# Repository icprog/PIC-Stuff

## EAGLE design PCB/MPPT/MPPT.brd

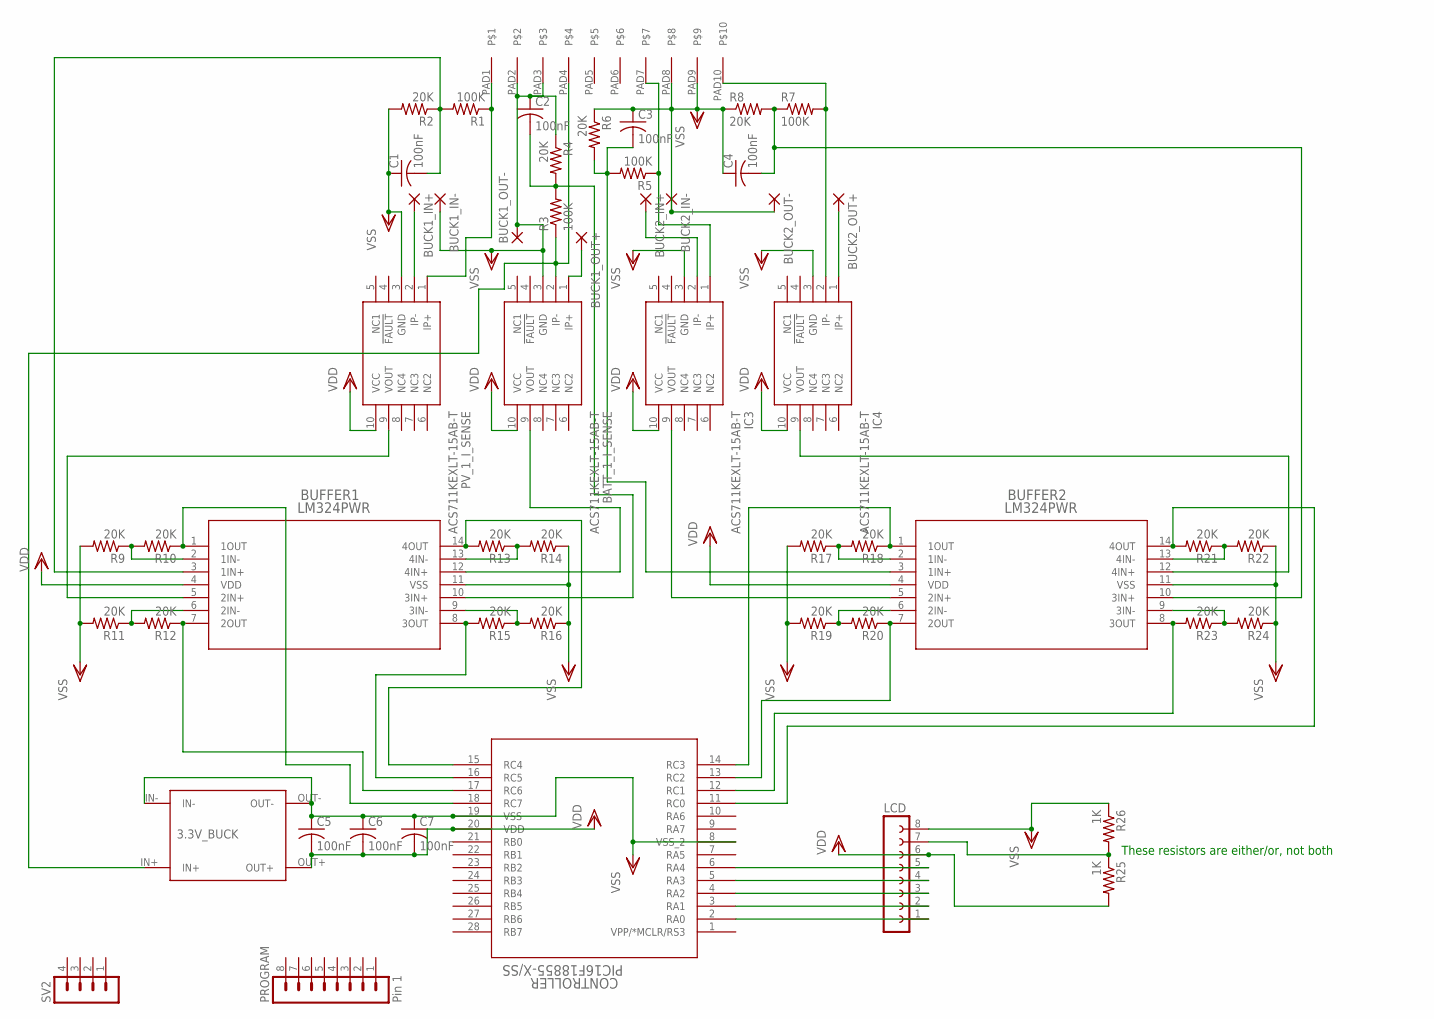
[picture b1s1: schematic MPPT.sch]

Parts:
3.3V_BUCK: TINY_BUCK
BATT_1_I_SENSE: ACS711KEXLT-15AB-T; EX-PACKAGE
BUCK1_IN+, BUCK1_IN-, BUCK1_OUT+, BUCK1_OUT-, BUCK2_IN+, BUCK2_IN-, BUCK2_OUT+, BUCK2_OUT-: 3,81/1,4
BUFFER1, BUFFER2: LM324PWR; PW14
C1, C2, C3, C4, C5, C6, C7: 100nF; C0603
CONTROLLER: PIC16F18855-X/SS; SSOP28_MC
IC3, IC4: ACS711KEXLT-15AB-T; EX-PACKAGE
LCD: FE08
PROGRAM: Pin 1; MA08-1
PV_1_I_SENSE: ACS711KEXLT-15AB-T; EX-PACKAGE
R1, R3, R5, R7: 100K; R0603
R2, R4, R6, R8, R9, R10, R11, R12, R13, R14, R15, R16, R17, R18, R19, R20, R21, R22, R23, R24: 20K; R0603
R25, R26: 1K; R0603
SV2: MA04-1
U$1: CONN-KF2EDG-10(5.08)E-BAYPLUGGABLECONNECTORS; CONN-KF2EDG-10(5.08)

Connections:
unnamed: PV_1_I_SENSE.1 (IP+), R1.1, U$1.PAD1
unnamed: BUFFER1.5 (2IN+), PV_1_I_SENSE.9 (VOUT)
unnamed: BUFFER1.3 (1IN+), C1.2, R1.2, R2.1
unnamed: BATT_1_I_SENSE.1 (IP+), BUCK1_OUT+.1
unnamed: BUFFER1.10 (3IN+), C2.2, R3.2, R4.2
unnamed: 3.3V_BUCK.IN+, BATT_1_I_SENSE.2 (IP-), R3.1, U$1.PAD4
unnamed: BUCK2_OUT+.1, IC4.1 (IP+)
unnamed: IC3.1 (IP+), R5.1, U$1.PAD7
unnamed: BUCK2_IN+.1, IC3.2 (IP-)
unnamed: BUFFER2.3 (1IN+), C3.2, R5.2, R6.2
unnamed: IC4.2 (IP-), R7.2, U$1.PAD10
unnamed: BUFFER2.10 (3IN+), C4.2, R7.1, R8.2
unnamed: BUCK1_IN+.1, PV_1_I_SENSE.2 (IP-)
unnamed: BUFFER1.9 (3IN-), R15.1, R16.2
unnamed: BUFFER1.1 (1OUT), CONTROLLER.18 (RC7), R10.1
unnamed: BUFFER1.6 (2IN-), R11.1, R12.2
unnamed: BUFFER1.7 (2OUT), CONTROLLER.17 (RC6), R12.1
unnamed: BUFFER1.13 (4IN-), R13.1, R14.2
unnamed: BUFFER1.2 (1IN-), R9.1, R10.2
unnamed: BUFFER1.14 (4OUT), CONTROLLER.15 (RC4), R13.2
unnamed: BUFFER1.8 (3OUT), CONTROLLER.16 (RC5), R15.2
unnamed: BATT_1_I_SENSE.9 (VOUT), BUFFER1.12 (4IN+)
unnamed: CONTROLLER.2 (RA0), LCD.1
unnamed: BUFFER2.1 (1OUT), CONTROLLER.14 (RC3), R18.1
unnamed: BUFFER2.7 (2OUT), CONTROLLER.13 (RC2), R20.1
unnamed: BUFFER2.6 (2IN-), R19.1, R20.2
unnamed: BUFFER2.14 (4OUT), CONTROLLER.11 (RC0), R21.2
unnamed: BUFFER2.13 (4IN-), R21.1, R22.2
unnamed: BUFFER2.8 (3OUT), CONTROLLER.12 (RC1), R23.2
unnamed: BUFFER2.9 (3IN-), R23.1, R24.2
unnamed: BUFFER2.2 (1IN-), R17.1, R18.2
unnamed: BUFFER2.5 (2IN+), IC3.9 (VOUT)
unnamed: BUFFER2.12 (4IN+), IC4.9 (VOUT)
unnamed: CONTROLLER.3 (RA1), LCD.2
unnamed: CONTROLLER.4 (RA2), LCD.3
unnamed: CONTROLLER.5 (RA3), LCD.4
unnamed: CONTROLLER.6 (RA4), LCD.5
unnamed: LCD.7, R25.1, R26.2
unnamed 38: CONTROLLER.22 (RB1); also elsewhere on the board
unnamed 39: CONTROLLER.21 (RB0); also elsewhere on the board
VDD: 3.3V_BUCK.OUT+, BATT_1_I_SENSE.10 (VCC), BUFFER1.4 (VDD), BUFFER2.4 (VDD), C5.2, C6.2, C7.2, CONTROLLER.20 (VDD), IC3.10 (VCC), IC4.10 (VCC), LCD.6, PV_1_I_SENSE.10 (VCC), R25.2; also elsewhere on the board
VSS: 3.3V_BUCK.IN-, 3.3V_BUCK.OUT-, BATT_1_I_SENSE.3 (GND), BUCK1_IN-.1, BUCK1_OUT-.1, BUCK2_IN-.1, BUCK2_OUT-.1, BUFFER1.11 (VSS), BUFFER2.11 (VSS), C1.1, C2.1, C3.1, C4.1, C5.1, C6.1, C7.1, CONTROLLER.8 (VSS_2), CONTROLLER.19 (VSS), IC3.3 (GND), IC4.3 (GND), LCD.8, PV_1_I_SENSE.3 (GND), R2.2, R4.1, R6.1, R8.1, R9.2, R11.2, R14.1, R16.1, R17.2, R19.2, R22.1, R24.1, R26.1, U$1.PAD2, U$1.PAD3, U$1.PAD8, U$1.PAD9; also elsewhere on the board

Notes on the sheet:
These resistors are either/or, not both

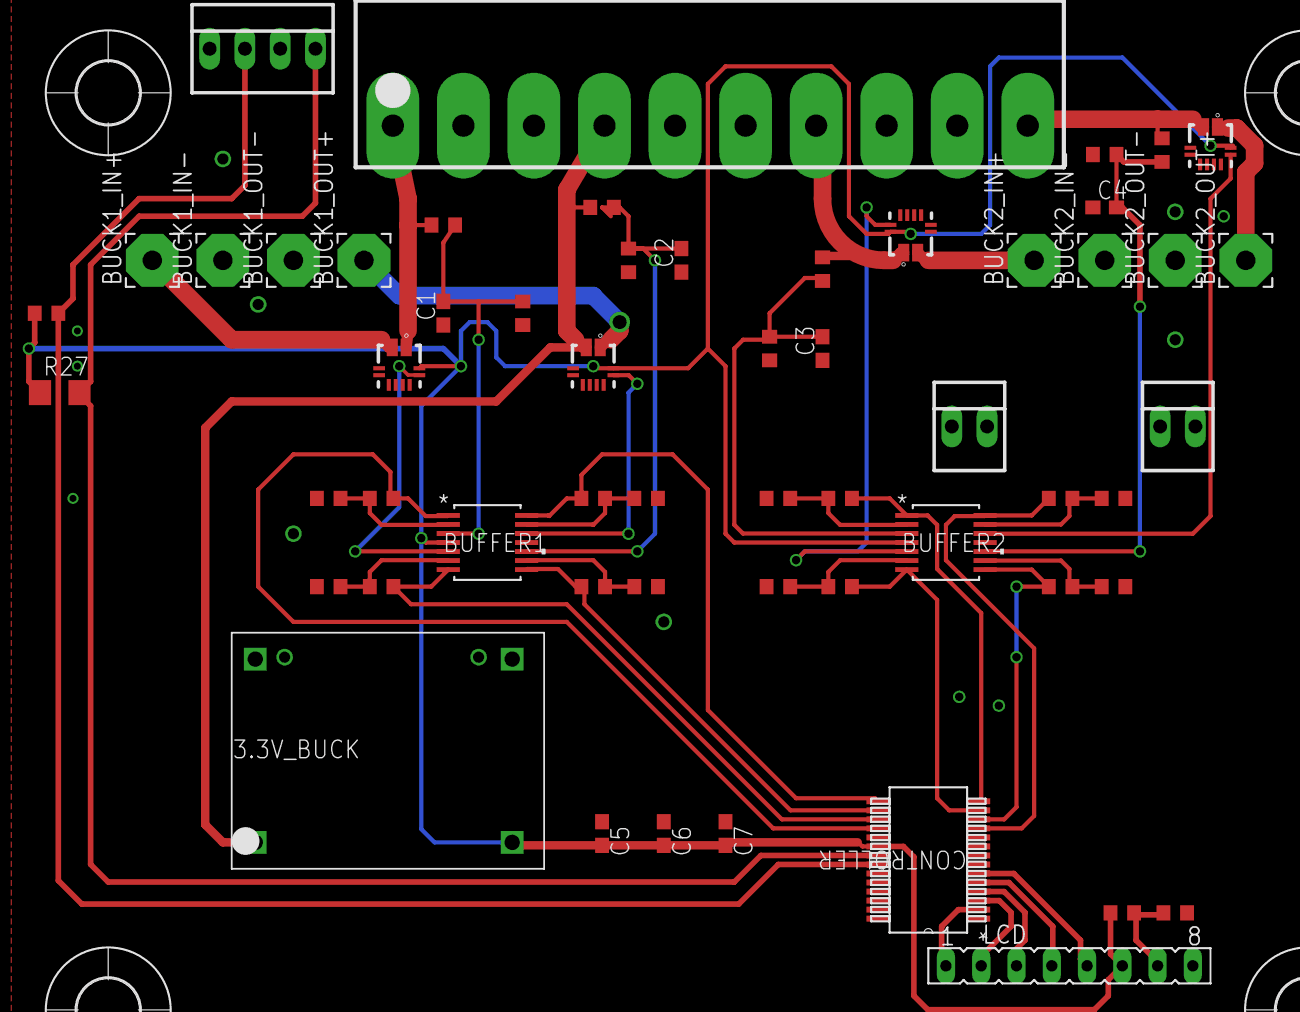
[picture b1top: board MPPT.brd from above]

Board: 2 copper layers, 60 parts (0 on the bottom side), 42 nets.

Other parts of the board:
R27: 10K; R1206
R28: 10K; R0603
U$2, U$3, U$4, U$5: 4,5
X1, X2: 22-23-2021
X3: 22-23-2041

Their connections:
unnamed 38: R28.2, X3.2; also elsewhere on the board
unnamed 39: R27.2, X3.4; also elsewhere on the board
VDD: R27.1, R28.1; also elsewhere on the board
VSS: X3.1, X3.3; also elsewhere on the board

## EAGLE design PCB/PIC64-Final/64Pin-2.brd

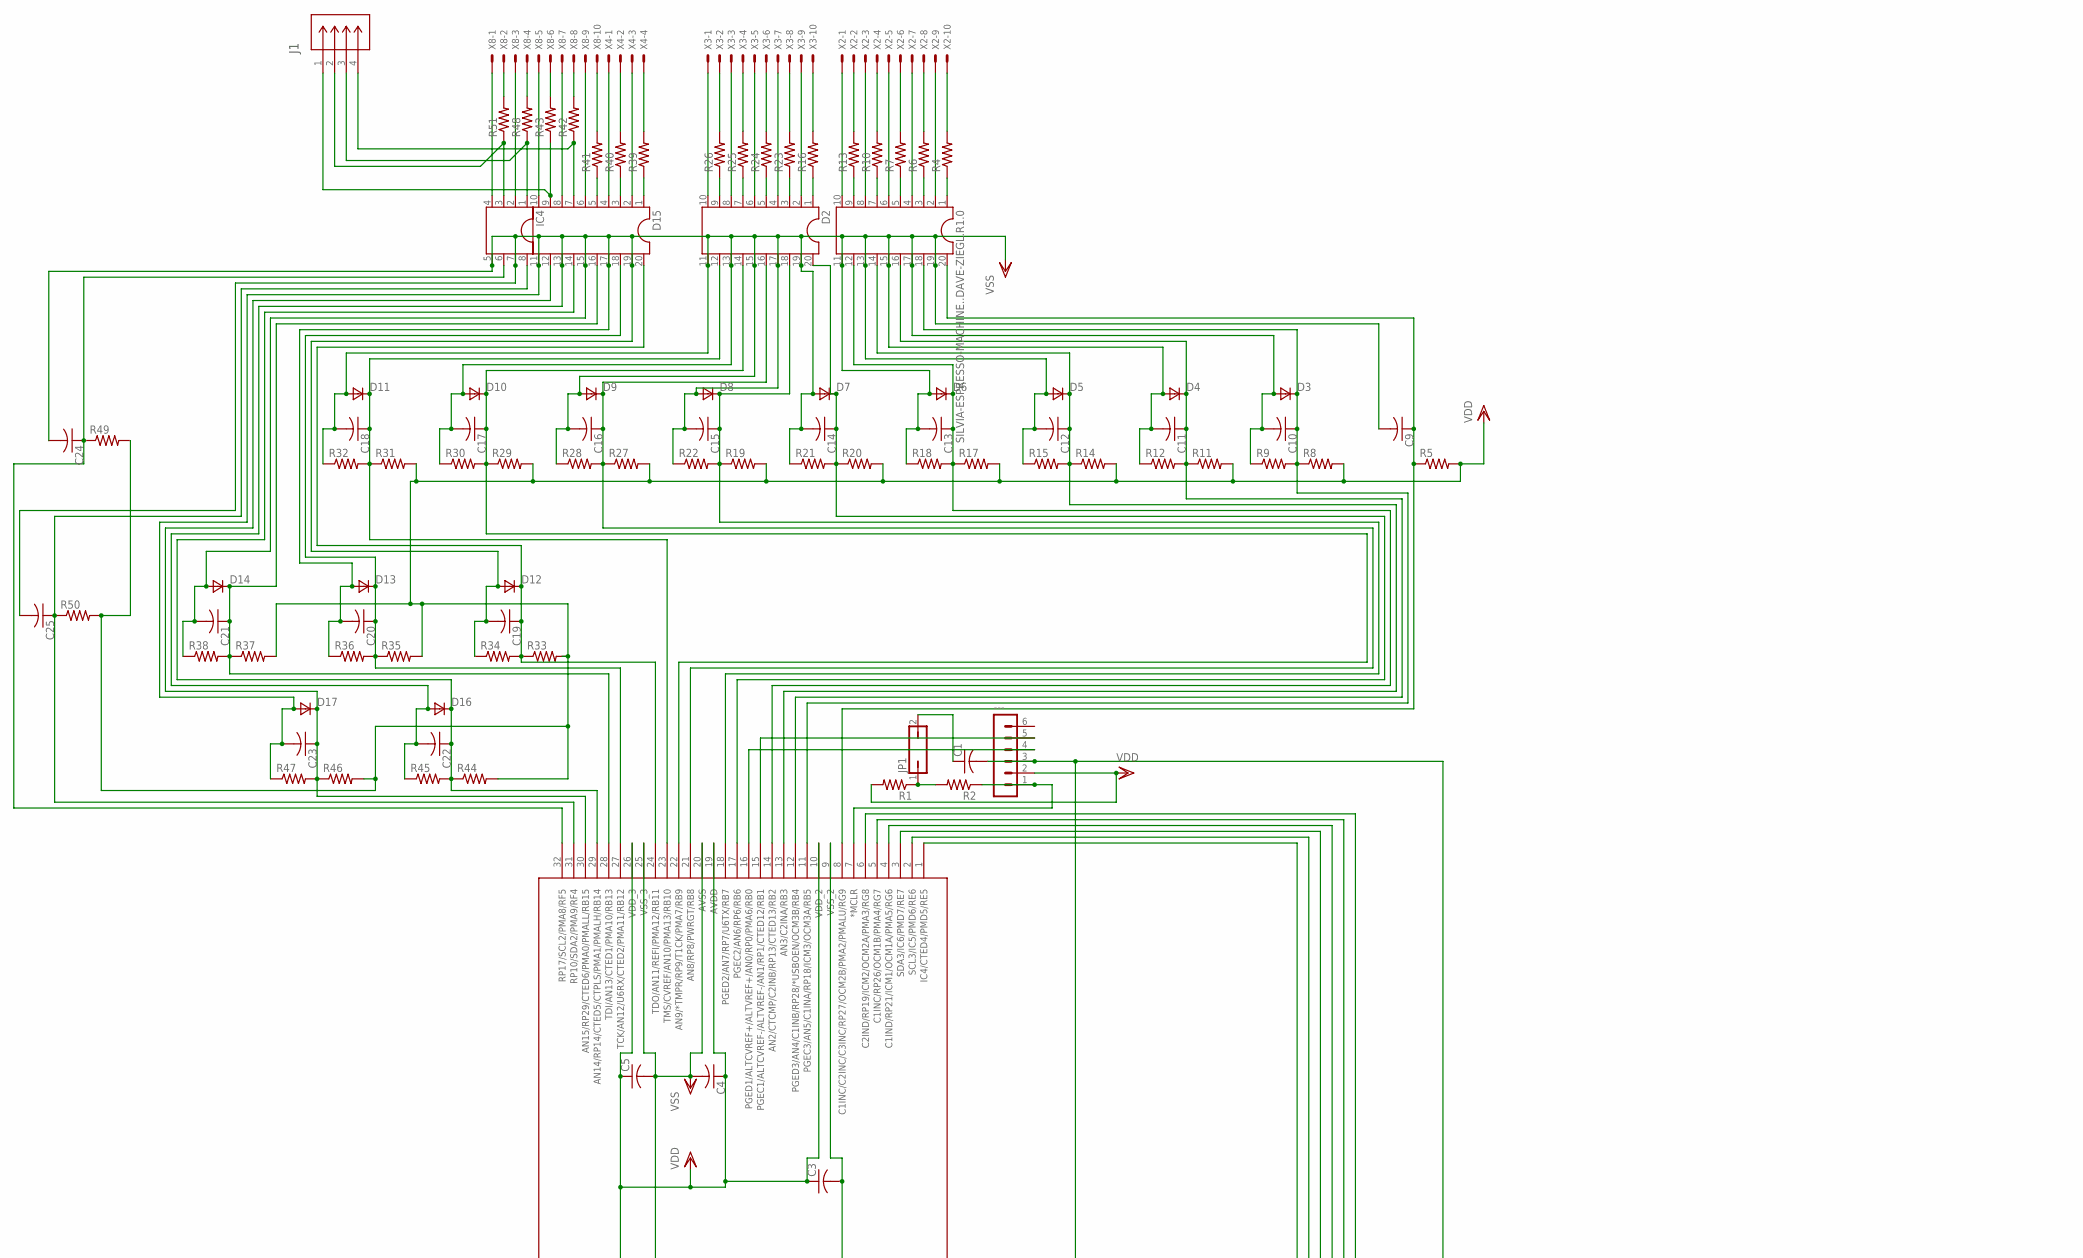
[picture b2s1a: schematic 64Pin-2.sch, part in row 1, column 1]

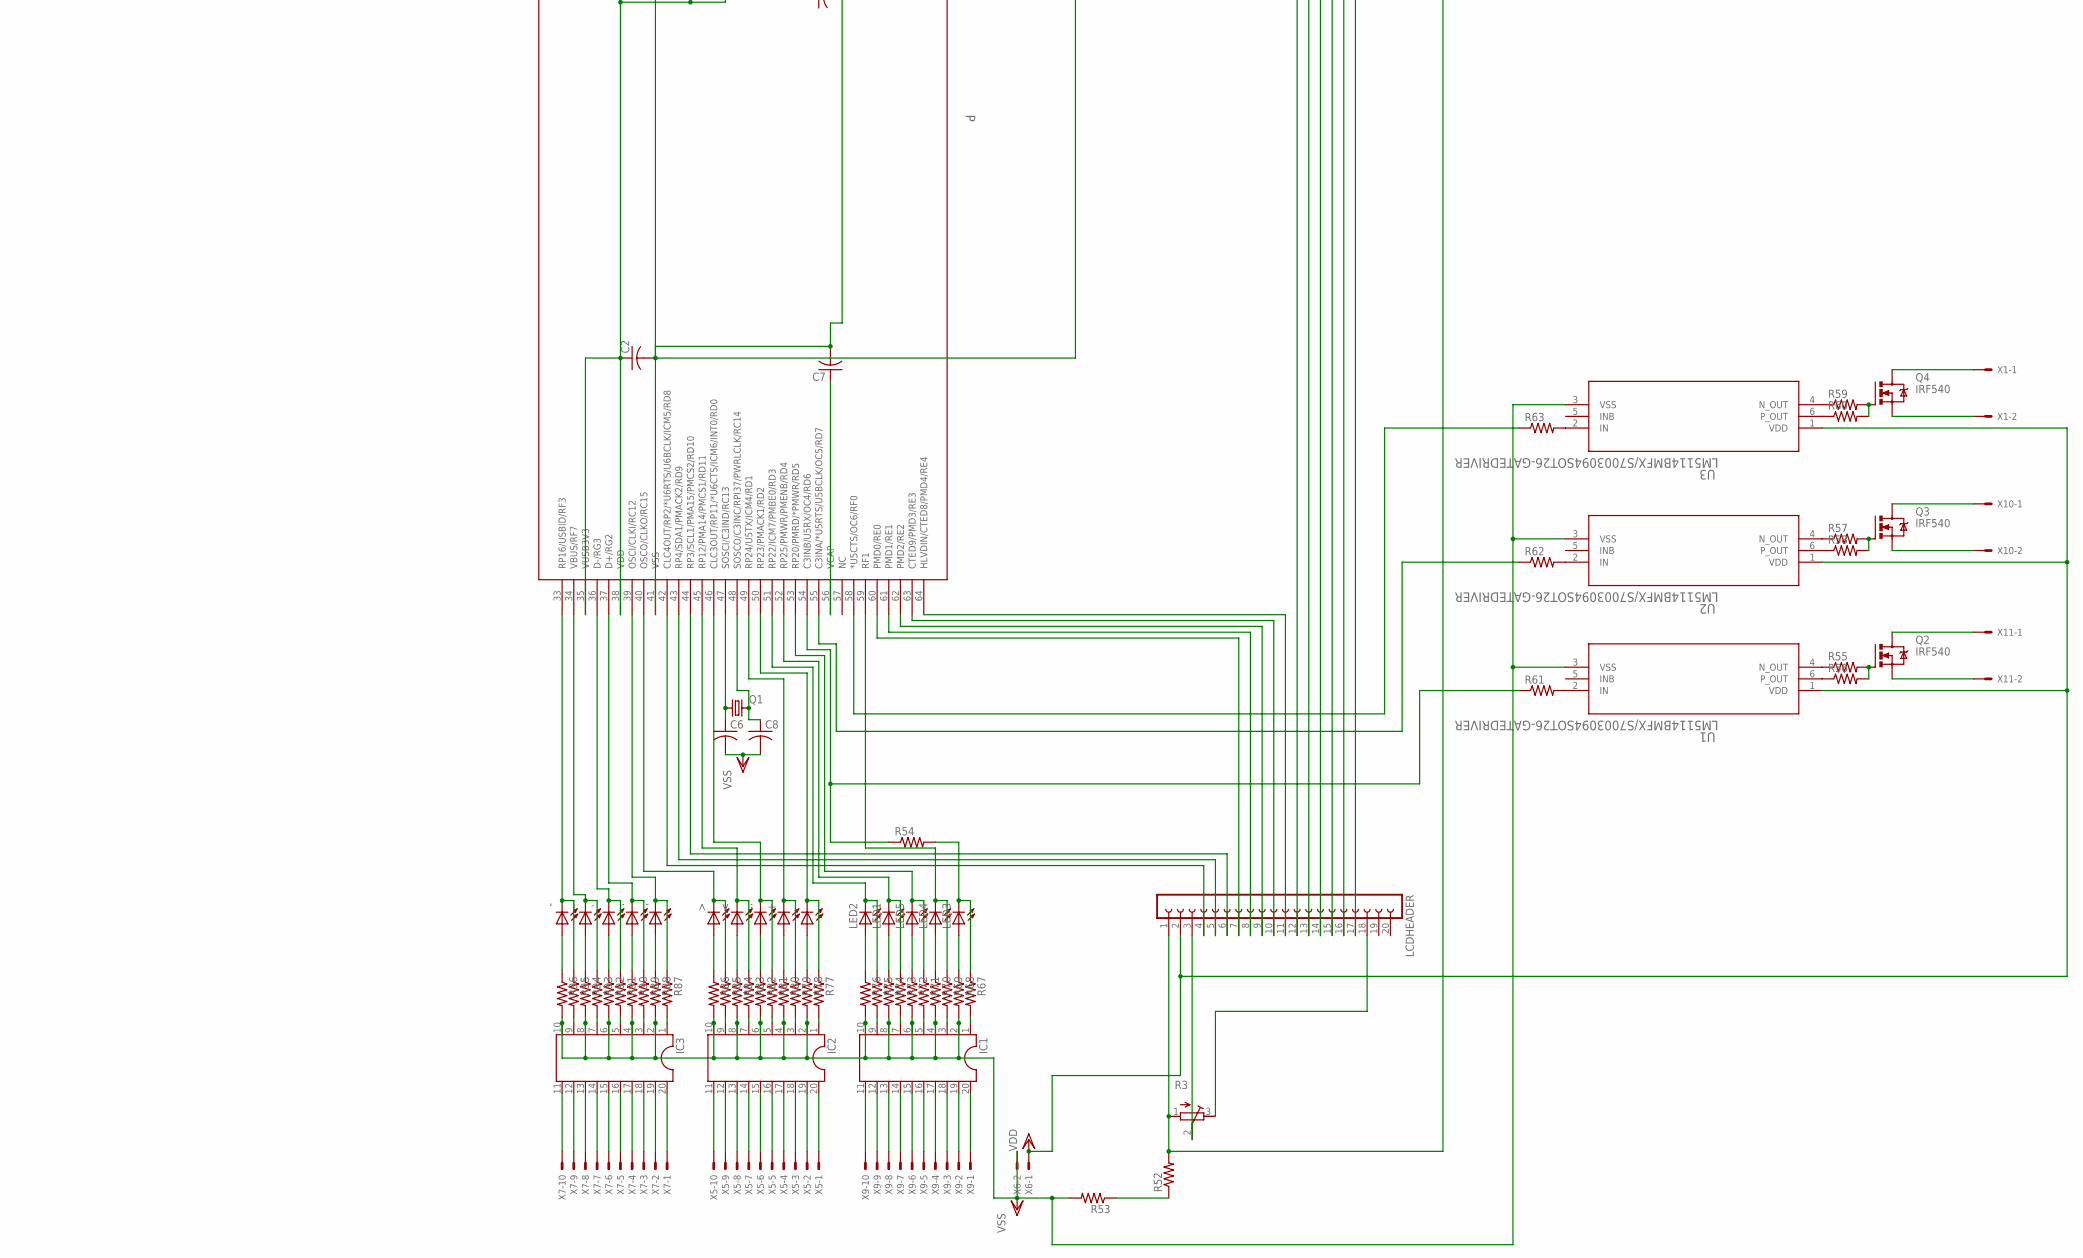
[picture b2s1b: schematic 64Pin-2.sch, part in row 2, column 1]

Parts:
+: LED_SML0603
,: LED_SML0603
-: LED_SML0603
--: LED_SML0603
---: MA06-1
., ..: LED_SML0603
<: LED_SML0603
>: LED_SML0603
C1, C2, C3, C4, C5, C6, C7, C8, C9, C10, C11, C12, C13, C14, C15, C16, C17, C18, C19, C20, C21, C22, C23, C24, C25: C0603
D2, D15: DIL20
D3, D4, D5, D6, D7, D8, D9, D10, D11, D12, D13, D14, D16, D17: SOD323
IC1, IC2, IC3: DIL20
IC4: DIL08
J1: 84952-4; CON4_SMT-RA_FCC-FPC2
JP1: JP1
LCDHEADER: FE20
LED1, LED2, LED3, LED4, LED5: LED_SML0603
P: TQFP64_10X10MC
Q1: TC26H
Q2, Q3, Q4: IRF540; TO220BV
R1, R2, R4, R5, R6, R7, R8, R9, R10, R11, R12, R13, R14, R15, R16, R17, R18, R19, R20, R21, R22, R23, R24, R25, R26, R27, R28, R29, R30, R31, R32, R33, R34, R35, R36, R37, R38, R39, R40, R41, R42, R43, R44, R45, R46, R47, R48, R49, R50, R51, R52, R53, R54, R55, R56, R57, R58, R59, R60, R61, R62, R63, R67, R68, R69, R70, R71, R72, R73, R74, R75, R76, R77, R78, R79, R80, R81, R82, R83, R84, R85, R86, R87, R88, R89, R90, R91, R92, R93, R94, R95, R96: R0603
R3: RTRIM3296W
SILVIA-ESPRESSO-MACHINE..DAVE-ZIEGL.R1.0: DIL20
U1, U2, U3: LM5114BMFX/S7003094SOT26-GATEDRIVER; MF06A
X1, X10, X11: KK-156-2
X2, X3, X5, X7, X8, X9: 22-23-2101
X4: 22-23-2041
X6: 22-23-2021
`: LED_SML0603
~: LED_SML0603

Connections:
MCLR: ---.1, P.7 (*MCLR), R2.1
unnamed: IC4.4, X8.1
unnamed: IC3.9, R95.2
unnamed: JP1.1, R1.1, R2.2
unnamed: R51.2, X8.2
unnamed: IC3.7, R93.2
unnamed: IC4.2, X8.3
unnamed: IC3.5, R91.2
unnamed: R48.2, X8.4
unnamed: IC3.3, R89.2
unnamed: D15.10, X8.5
unnamed: IC4.1, J1.3, R48.1
unnamed: C1.1, JP1.2
unnamed: IC4.3, J1.2, R51.1
unnamed: R43.2, X8.6
unnamed: D15.8, X8.7
unnamed: R42.2, X8.8
unnamed: D15.6, X8.9
unnamed: IC3.1, R87.2
unnamed: R41.2, X8.10
unnamed: D15.4, X4.1
unnamed: R40.2, X4.2
unnamed: D15.2, X4.3
unnamed: R39.2, X4.4
unnamed: R57.1, U2.4 (N_OUT)
unnamed: R58.1, U2.6 (P_OUT)
unnamed: R55.1, U1.4 (N_OUT)
unnamed: -.A, R96.1
unnamed: --.A, R94.1
unnamed: R92.1, `.A
unnamed: ..A, R90.1
unnamed: ,.A, R88.1
unnamed: R56.1, U1.6 (P_OUT)
unnamed: >.A, R86.1
unnamed: IC2.9, R85.2
unnamed 44: SILVIA-ESPRESSO-MACHINE..DAVE-ZIEGL.R1.0.6, X2.5; also elsewhere on the board
unnamed: R10.2, X2.4
unnamed 46: Q4.D, X1.1; also elsewhere on the board
unnamed: IC2.7, R83.2
unnamed: Q2.G, R55.2, R56.2
unnamed: IC2.5, R81.2
unnamed: Q3.G, R57.2, R58.2
unnamed: IC2.3, R79.2
unnamed: R59.1, U3.4 (N_OUT)
unnamed: IC2.1, R77.2
unnamed 54: R10.1, SILVIA-ESPRESSO-MACHINE..DAVE-ZIEGL.R1.0.7; also elsewhere on the board
unnamed: R78.1, ~.A
unnamed: +.A, R80.1
unnamed: ...A, R82.1
unnamed: <.A, R84.1
unnamed: R60.1, U3.6 (P_OUT)
unnamed: IC1.9, R75.2
unnamed: Q4.G, R59.2, R60.2
unnamed: IC1.7, R73.2
unnamed 63: LCDHEADER.20; also elsewhere on the board
unnamed: IC1.5, R71.2
unnamed 65: Q3.D, X10.1; also elsewhere on the board
unnamed: IC1.3, R69.2
unnamed: IC1.1, R67.2
unnamed: LED3.A, R68.1
unnamed: LED4.A, R70.1
unnamed: LED5.A, R72.1
unnamed: LED1.A, R74.1
unnamed: LED2.A, R76.1
unnamed 73: Q2.D, X11.1; also elsewhere on the board
unnamed: LCDHEADER.19, R52.1, R53.1
unnamed: R61.2, U1.2 (IN)
unnamed: R62.2, U2.2 (IN)
unnamed: R63.2, U3.2 (IN)
unnamed: P.55 (C3INA/*U5RTS/U5BCLK/OC5/RD7), R62.1
unnamed: P.58 (*U5CTS/OC6/RF0), R63.1
unnamed: D15.9, J1.1, R43.1
unnamed: D15.7, J1.4, R42.1
unnamed: D15.5, R41.1
unnamed: D15.3, R40.1
unnamed: D15.1, R39.1
unnamed: D2.10, X3.1
unnamed: D2.9, R26.1
unnamed: D2.8, X3.3
unnamed: R26.2, X3.2
unnamed: R25.2, X3.4
unnamed: D2.6, X3.5
unnamed: D2.7, R25.1
unnamed: D2.4, X3.7
unnamed: D2.3, R23.1
unnamed: R23.2, X3.8
unnamed: D2.2, X3.9
unnamed: D2.1, R16.1
unnamed: R16.2, X3.10
unnamed 98: SILVIA-ESPRESSO-MACHINE..DAVE-ZIEGL.R1.0.10, X2.1; also elsewhere on the board
unnamed: R13.2, X2.2
unnamed 100: R13.1, SILVIA-ESPRESSO-MACHINE..DAVE-ZIEGL.R1.0.9; also elsewhere on the board
unnamed 101: SILVIA-ESPRESSO-MACHINE..DAVE-ZIEGL.R1.0.8, X2.3; also elsewhere on the board
unnamed: D2.5, R24.1
unnamed: R24.2, X3.6
unnamed: R7.2, X2.6
unnamed 105: R7.1, SILVIA-ESPRESSO-MACHINE..DAVE-ZIEGL.R1.0.5; also elsewhere on the board
unnamed 106: SILVIA-ESPRESSO-MACHINE..DAVE-ZIEGL.R1.0.4, X2.7; also elsewhere on the board
unnamed: R6.2, X2.8
unnamed 108: R6.1, SILVIA-ESPRESSO-MACHINE..DAVE-ZIEGL.R1.0.3; also elsewhere on the board
unnamed 109: SILVIA-ESPRESSO-MACHINE..DAVE-ZIEGL.R1.0.2, X2.9; also elsewhere on the board
unnamed: R4.2, X2.10
unnamed 111: R4.1, SILVIA-ESPRESSO-MACHINE..DAVE-ZIEGL.R1.0.1; also elsewhere on the board
unnamed 112: LCDHEADER.3, R3.2 (S); also elsewhere on the board
unnamed 113: LCDHEADER.18, R3.3 (E); also elsewhere on the board
OUT: LED3.C, R54.2, R67.1
OUT1-1: IC3.11, X7.10
OUT1-2: IC3.12, X7.9
OUT2-1: IC3.13, X7.8
OUT2-2: IC3.14, X7.7
OUT3-1: IC3.15, X7.6
OUT3-2: IC3.16, X7.5
OUT4-1: IC3.17, X7.4
OUT4-2: IC3.18, X7.3
OUT5-1: IC3.19, X7.2
OUT5-2: IC3.20, X7.1
OUT6-1: IC2.11, X5.10
OUT6-2: IC2.12, X5.9
OUT7-1: IC2.13, X5.8
OUT7-2: IC2.14, X5.7
OUT8-1: IC2.15, X5.6
OUT8-2: IC2.16, X5.5
OUT9-1: IC2.17, X5.4
OUT9-2: IC2.18, X5.3
OUT10-1: IC2.19, X5.2
OUT10-2: IC2.20, X5.1
OUT11-1: IC1.11, X9.10
OUT11-2: IC1.12, X9.9
OUT12-1: IC1.13, X9.8
OUT12-2: IC1.14, X9.7
OUT13-1: IC1.15, X9.6
OUT13-2: IC1.16, X9.5
OUT14-1: IC1.17, X9.4
OUT14-2: IC1.18, X9.3
OUT15-1: IC1.19, X9.2
OUT15-2: IC1.20, X9.1
PGEC1: ---.5, P.15 (PGEC1/ALTCVREF-/ALTVREF-/AN1/RP1/CTED12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)
PGECD: ---.4, P.16 (PGED1/ALTCVREF+/ALTVREF+/AN0/RP0/PMA6/R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)
PIN1: LCDHEADER.12, P.1 (IC4/CTED4/PMD5/RE5)
PIN2: LCDHEADER.13, P.2 (SCL3/IC5/PMD6/RE6)
PIN3: LCDHEADER.14, P.3 (SDA3/IC6/PMD7/RE7)
PIN4: LCDHEADER.15, P.4 (C1IND/RP21/ICM1/OCM1A/PMA5/RG6)
PIN5: LCDHEADER.16, P.5 (C1INC/RP26/OCM1B/PMA4/RG7)
PIN6: LCDHEADER.17, P.6 (C2IND/RP19/ICM2/OCM2A/PMA3/RG8)
PIN8: C9.1, P.8 (C1INC/C2INC/C3INC/RP27/OCM2B/PMA2/PMALU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), R5.1, SILVIA-ESPRESSO-MACHINE..DAVE-ZIEGL.R1.0.20; also elsewhere on the board
PIN11: C10.1, D3.1 (C), P.11 (PGEC3/AN5/C1INA/RP18/ICM3/OCM3A/RB5), R8.1, R9.2, SILVIA-ESPRESSO-MACHINE..DAVE-ZIEGL.R1.0.18; also elsewhere on the board
PIN12: C11.1, D4.1 (C), P.12 (PGED3/AN4/C1INB/RP28/*USBOEN/OCM3B/RB4), R11.1, R12.2, SILVIA-ESPRESSO-MACHINE..DAVE-ZIEGL.R1.0.16; also elsewhere on the board
PIN13: C12.1, D5.1 (C), P.13 (AN3/C2INA/RB3), R14.1, R15.2, SILVIA-ESPRESSO-MACHINE..DAVE-ZIEGL.R1.0.14; also elsewhere on the board
PIN14: C13.1, D6.1 (C), P.14 (AN2/CTCMP/C2INB/RP13/CTED13/RB2), R17.1, R18.2, SILVIA-ESPRESSO-MACHINE..DAVE-ZIEGL.R1.0.12; also elsewhere on the board
PIN17: C14.1, D2.20, D7.1 (C), P.17 (PGEC2/AN6/RP6/RB6), R20.1, R21.2
PIN18: C15.1, D2.18, D8.1 (C), P.18 (PGED2/AN7/RP7/U6TX/RB7), R19.1, R22.2
PIN21: C16.1, D2.16, D9.1 (C), P.21 (AN8/RP8/PWRGT/RB8), R27.1, R28.2
PIN22: C17.1, D2.14, D10.1 (C), P.22 (AN9/*TMPR/RP9/T1CK/PMA7/RB9), R29.1, R30.2
PIN23: C18.1, D2.12, D11.1 (C), P.23 (TMS/CVREF/AN10/PMA13/RB10), R31.1, R32.2
PIN24: C19.1, D12.1 (C), D15.20, P.24 (TDO/AN11/REFI/PMA12/RB11), R33.1, R34.2
PIN27: C20.1, D13.1 (C), D15.18, P.27 (TCK/AN12/U6RX/CTED2/PMA11/RB12), R35.1, R36.2
PIN28: C21.1, D14.1 (C), D15.16, P.28 (TDI/AN13/CTED1/PMA10/RB13), R37.1, R38.2
PIN29: C22.1, D15.14, D16.1 (C), P.29 (AN14/RP14/CTED5/CTPLS/PMA1/PMALH/RB14), R44.1, R45.2
PIN30: C23.1, D15.12, D17.1 (C), P.30 (AN15/RP29/CTED6/PMA0/PMALL/RB15), R46.1, R47.2
PIN31: C25.1, IC4.8, P.31 (RP10/SDA2/PMA9/RF4), R50.1
PIN32: C24.1, IC4.6, P.32 (RP17/SCL2/PMA8/RF5), R49.1
PIN33: -.C, P.33 (RP16/USBID/RF3), R95.1
PIN34: --.C, P.34 (VBUS/RF7), R93.1
PIN36: P.36 (D-/RG3), R91.1, `.C
PIN37: ..C, P.37 (D+/RG2), R89.1
PIN39: ,.C, P.39 (OSCI/CLKI/RC12), R87.1
PIN40: >.C, P.40 (OSCO/CLKO/RC15), R85.1
PIN42: LCDHEADER.4, P.42 (CLC4OUT/RP2/*U6RTS/U6BCLK/ICM5/RD8)
PIN43: LCDHEADER.5, P.43 (RP4/SDA1/PMACK2/RD9)
PIN44: LCDHEADER.6, P.44 (RP3/SCL1/PMA15/PMCS2/RD10)
PIN45: <.C, P.45 (RP12/PMA14/PMCS1/RD11), R83.1
PIN46: ...C, P.46 (CLC3OUT/RP11/*U6CTS/ICM6/INT0/RD0), R81.1
PIN49: +.C, P.49 (RP24/U5TX/ICM4/RD1), R79.1
PIN50: P.50 (RP23/PMACK1/RD2), R77.1, ~.C
PIN51: LED2.C, P.51 (RP22/ICM7/PMBE0/RD3), R75.1
PIN52: LED1.C, P.52 (RP25/PMWR/PMENB/RD4), R73.1
PIN53: LED5.C, P.53 (RP20/PMRD/*PMWR/RD5), R71.1
PIN54: P.54 (C3INB/U5RX/OC4/RD6), R54.1, R61.1
PIN59: LED4.C, P.59 (RF1), R69.1
PIN60: LCDHEADER.7, P.60 (PMD0/RE0)
PIN61: LCDHEADER.8, P.61 (PMD1/RE1)
PIN62: LCDHEADER.9, P.62 (PMD2/RE2)
PIN63: LCDHEADER.10, P.63 (CTED9/PMD3/RE3)
PIN64: LCDHEADER.11, P.64 (HLVDIN/CTED8/PMD4/RE4)
SOSCI: C6.1, P.47 (SOSCI/C3IND/RC13), Q1.1
SOSCO: C8.1, P.48 (SOSCO/C3INC/RPI37/PWRLCLK/RC14), Q1.2
VCAP: C7.1, P.56 (VCAP)
VDD: ---.2, C2.1, C3.1, C4.1, C5.1, LCDHEADER.2, P.10 (VDD_2), P.19 (AVDD), P.26 (VDD_3), P.35 (VUSB3V3), P.38 (VDD), R1.2, R5.2, R8.2, R11.2, R14.2, R17.2, R19.2, R20.2, R27.2, R29.2, R31.2, R33.2, R35.2, R37.2, R44.2, R46.2, R49.2, R50.2, U1.1 (VDD), U2.1 (VDD), U3.1 (VDD), X6.1; also elsewhere on the board

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
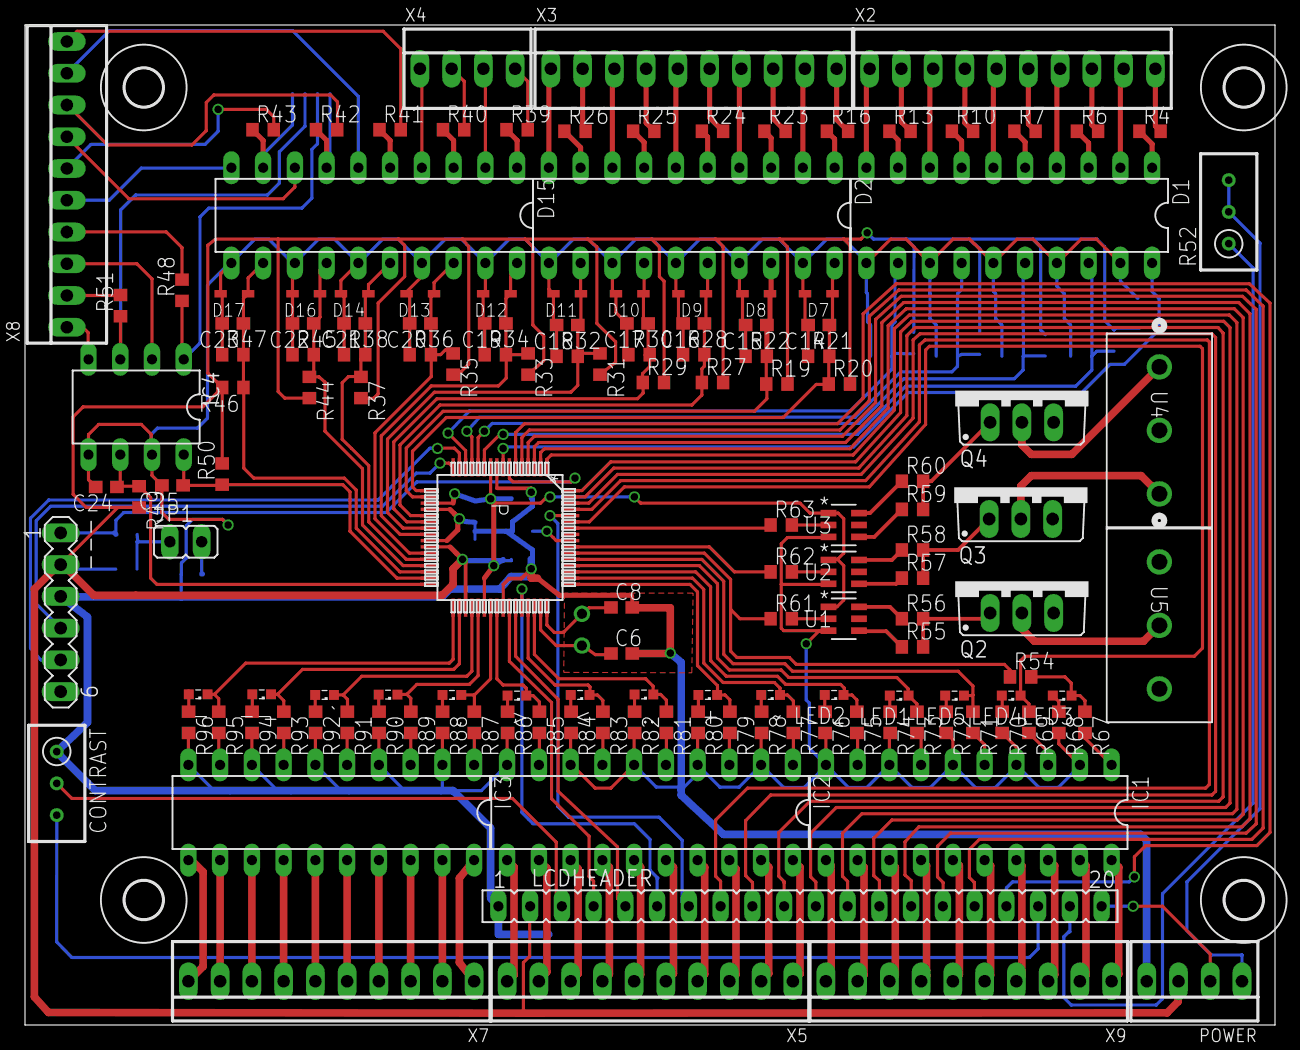
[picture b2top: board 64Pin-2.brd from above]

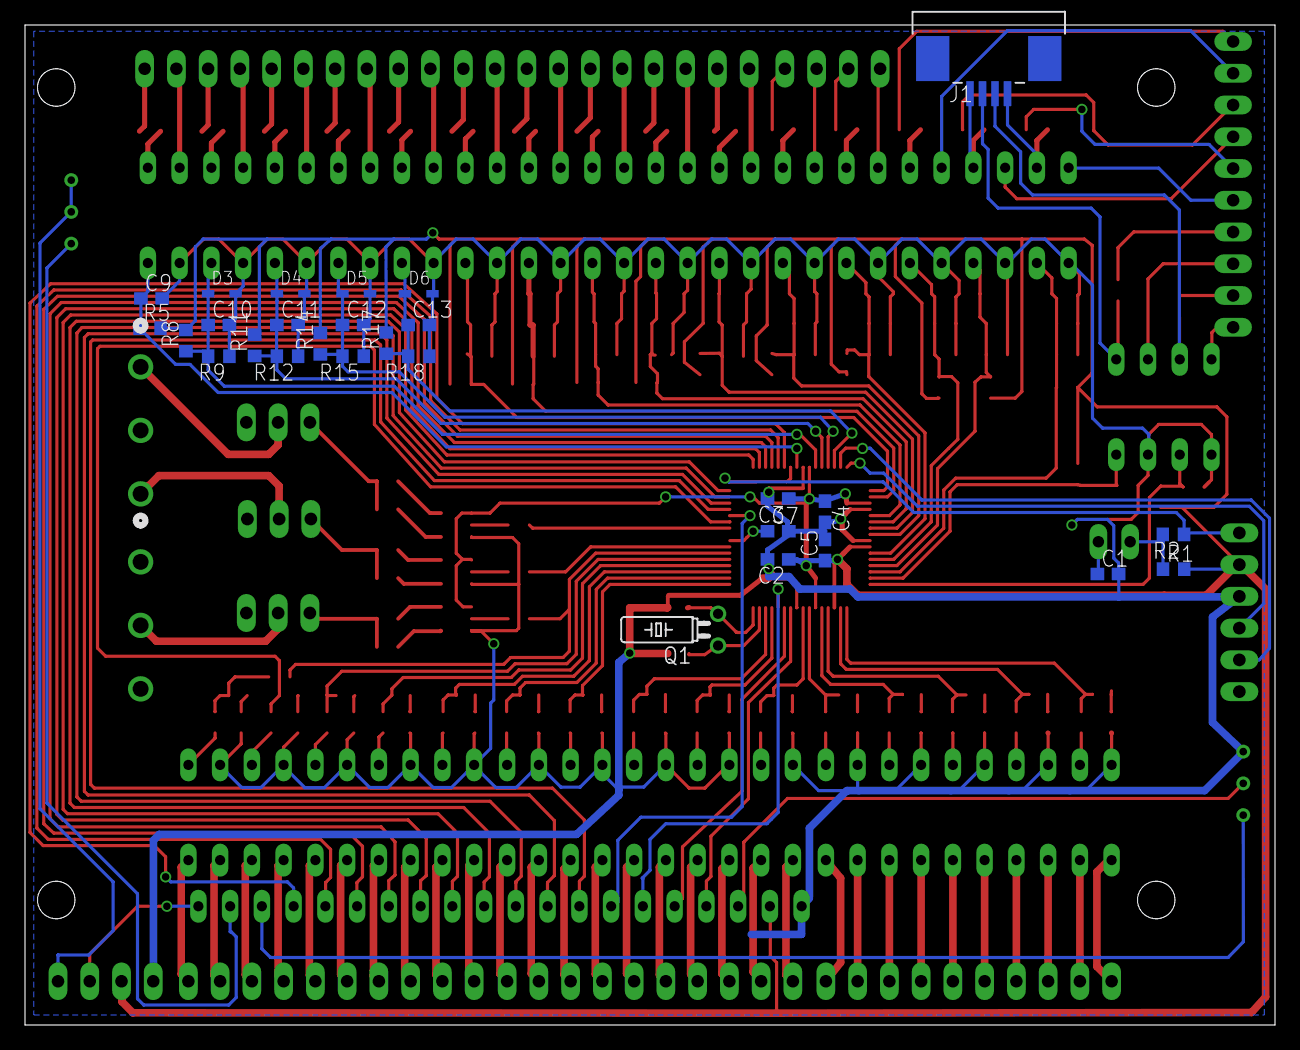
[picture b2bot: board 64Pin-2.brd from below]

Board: 2 copper layers, 100.0 x 80.0 mm, 179 parts (28 on the bottom side), 190 nets.

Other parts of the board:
CONTRAST: RTRIM3296W
D1: DIL20
POWER: 22-23-2041
U4, U5: 282837-3
U$5, U$6, U$7, U$8: 3,0

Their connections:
unnamed 44: D1.6; also elsewhere on the board
unnamed 46: U4.1; also elsewhere on the board
unnamed 54: D1.7; also elsewhere on the board
unnamed 63: POWER.2; also elsewhere on the board
unnamed 65: U4.3; also elsewhere on the board
unnamed 73: U5.2; also elsewhere on the board
unnamed 98: D1.10; also elsewhere on the board
unnamed 100: D1.9; also elsewhere on the board
unnamed 101: D1.8; also elsewhere on the board
unnamed 105: D1.5; also elsewhere on the board
unnamed 106: D1.4; also elsewhere on the board
unnamed 108: D1.3; also elsewhere on the board
unnamed 109: D1.2; also elsewhere on the board
unnamed 111: D1.1; also elsewhere on the board
unnamed 112: CONTRAST.2; also elsewhere on the board
unnamed 113: CONTRAST.3; also elsewhere on the board
PIN8: D1.20; also elsewhere on the board
PIN11: D1.18; also elsewhere on the board
PIN12: D1.16; also elsewhere on the board
PIN13: D1.14; also elsewhere on the board
PIN14: D1.12; also elsewhere on the board
VDD: POWER.3; also elsewhere on the board

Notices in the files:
parts and their libraries:
COPYRIGHT: Copyright (C) 2016 Accelerated Designs. All rights reserved
